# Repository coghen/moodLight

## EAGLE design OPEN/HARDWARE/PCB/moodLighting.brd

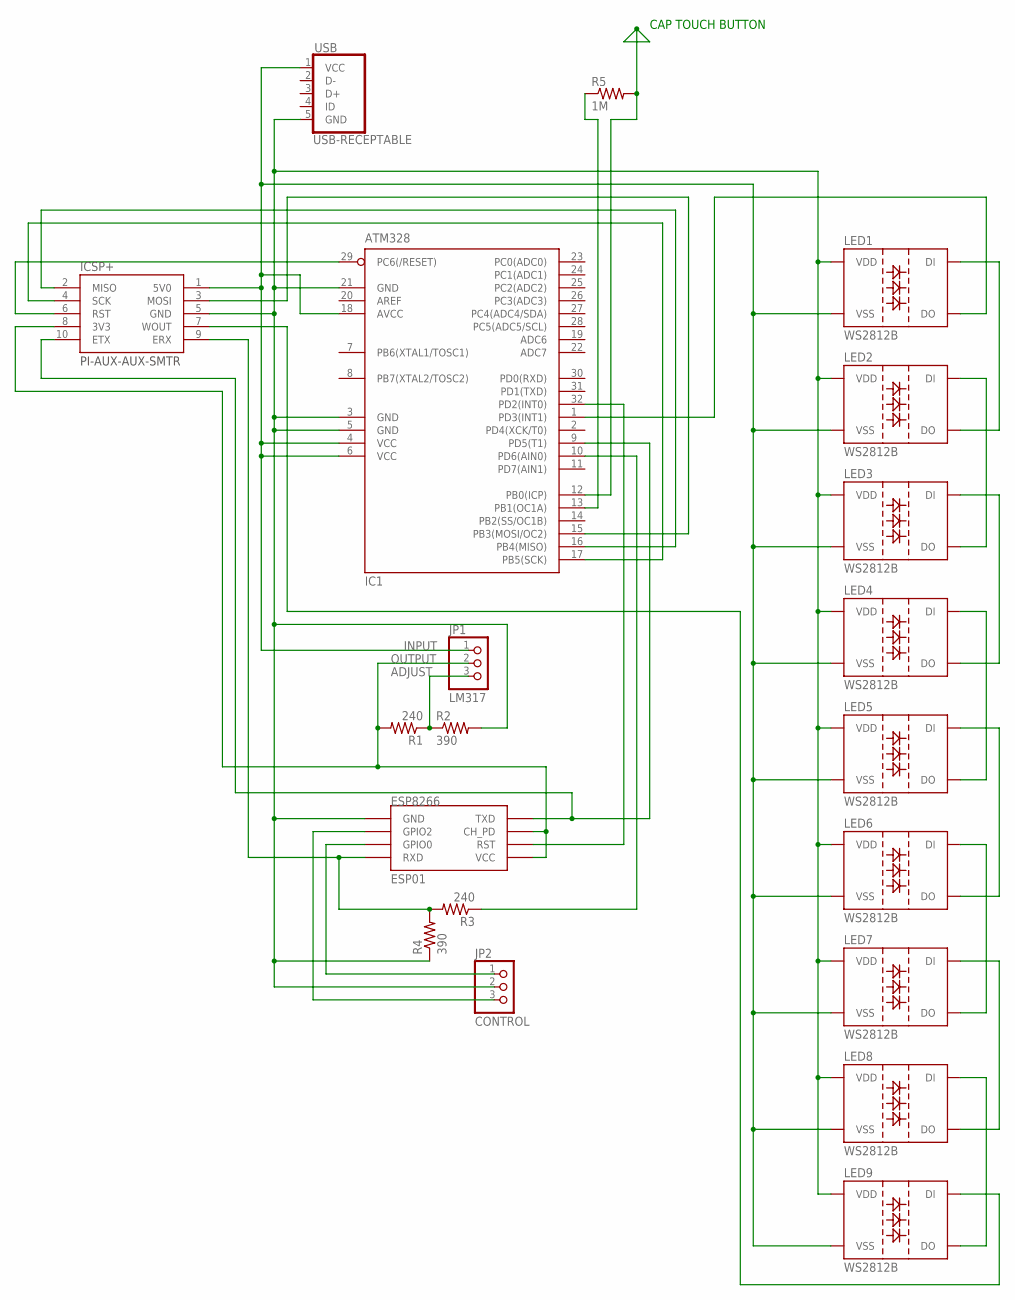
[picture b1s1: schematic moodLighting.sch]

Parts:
ESP8266: ESP01
IC1: ATM328; TQFP32-08
ICSP+: PI-AUX-AUX-SMTR; GPIO-AUX-CONNECTOR-SMT-REV
JP1: LM317; 1X03
JP2: CONTROL; 1X03
LED1, LED2, LED3, LED4, LED5, LED6, LED7, LED8, LED9: WS2812B
R1, R3: 240; R0805
R2, R4: 390; R0805
R5: 1M; R0805
USB: USB-RECEPTABLE; FCI-10103594-0001LF

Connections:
CAP: IC1.12 (PB0(ICP)), R5.2
unnamed: IC1.4 (VCC), IC1.6 (VCC), IC1.18 (AVCC), ICSP+.1 (5V0), JP1.1, LED1.3 (VSS), LED2.3 (VSS), LED3.3 (VSS), LED4.3 (VSS), LED5.3 (VSS), LED6.3 (VSS), LED7.3 (VSS), LED8.3 (VSS), LED9.3 (VSS), USB.1 (VCC)
unnamed: ESP8266.RST, IC1.32 (PD2(INT0))
unnamed: IC1.1 (PD3(INT1)), LED1.2 (DO)
unnamed: LED1.4 (DI), LED2.2 (DO)
unnamed: LED2.4 (DI), LED3.2 (DO)
unnamed: LED3.4 (DI), LED4.2 (DO)
unnamed: LED4.4 (DI), LED5.2 (DO)
unnamed: LED5.4 (DI), LED6.2 (DO)
unnamed: LED6.4 (DI), LED7.2 (DO)
unnamed: LED7.4 (DI), LED8.2 (DO)
unnamed: LED8.4 (DI), LED9.2 (DO)
unnamed: ICSP+.7 (WOUT), LED9.4 (DI)
unnamed: ESP8266.CH_PD, ESP8266.VCC, ICSP+.8 (3V3), JP1.2, R1.2
unnamed: JP1.3, R1.1, R2.1
unnamed: ESP8266.GND, IC1.3 (GND), IC1.5 (GND), IC1.21 (GND), ICSP+.5 (GND), JP2.2, LED1.1 (VDD), LED2.1 (VDD), LED3.1 (VDD), LED4.1 (VDD), LED5.1 (VDD), LED6.1 (VDD), LED7.1 (VDD), LED8.1 (VDD), LED9.1 (VDD), R2.2, R4.1, USB.5 (GND)
unnamed: ESP8266.TX (TXD), IC1.9 (PD5(T1)), ICSP+.10 (ETX)
unnamed: IC1.15 (PB3(MOSI/OC2)), ICSP+.3 (MOSI)
unnamed: IC1.16 (PB4(MISO)), ICSP+.2 (MISO)
unnamed: IC1.10 (PD6(AIN0)), R3.1
unnamed: ESP8266.RX (RXD), ICSP+.9 (ERX), R3.2, R4.2
unnamed: ESP8266.GPIO0, JP2.1
unnamed: IC1.17 (PB5(SCK)), ICSP+.4 (SCK)
unnamed: IC1.29 (PC6(/RESET)), ICSP+.6 (RST)
unnamed: ESP8266.GPIO2, JP2.3
unnamed: IC1.13 (PB1(OC1A)), R5.1

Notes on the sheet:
INPUT
OUTPUT
ADJUST
CAP TOUCH BUTTON

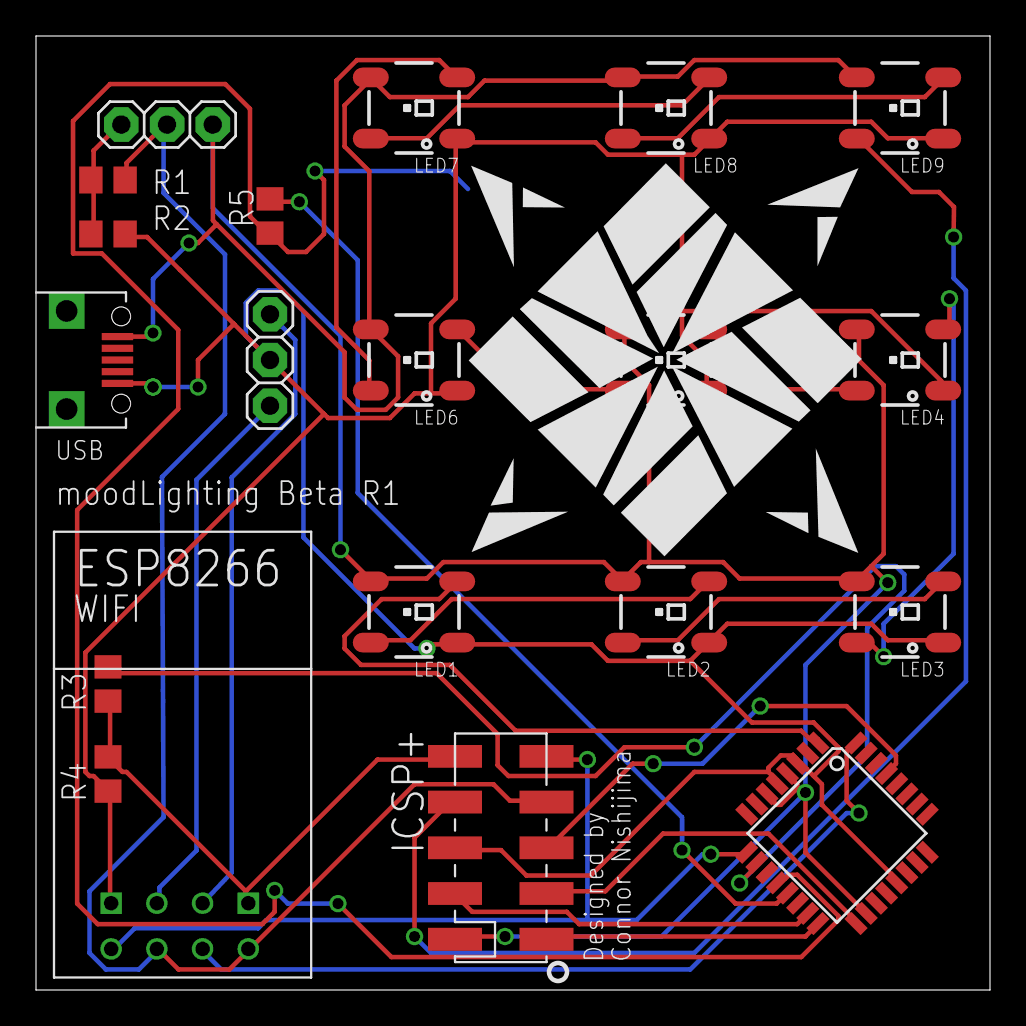
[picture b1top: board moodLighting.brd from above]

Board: 2 copper layers, 53.0 x 53.0 mm, 20 parts (0 on the bottom side), 26 nets.

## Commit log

2015-10-05 :circus_tent: Added .gitattributes & .gitignore files
